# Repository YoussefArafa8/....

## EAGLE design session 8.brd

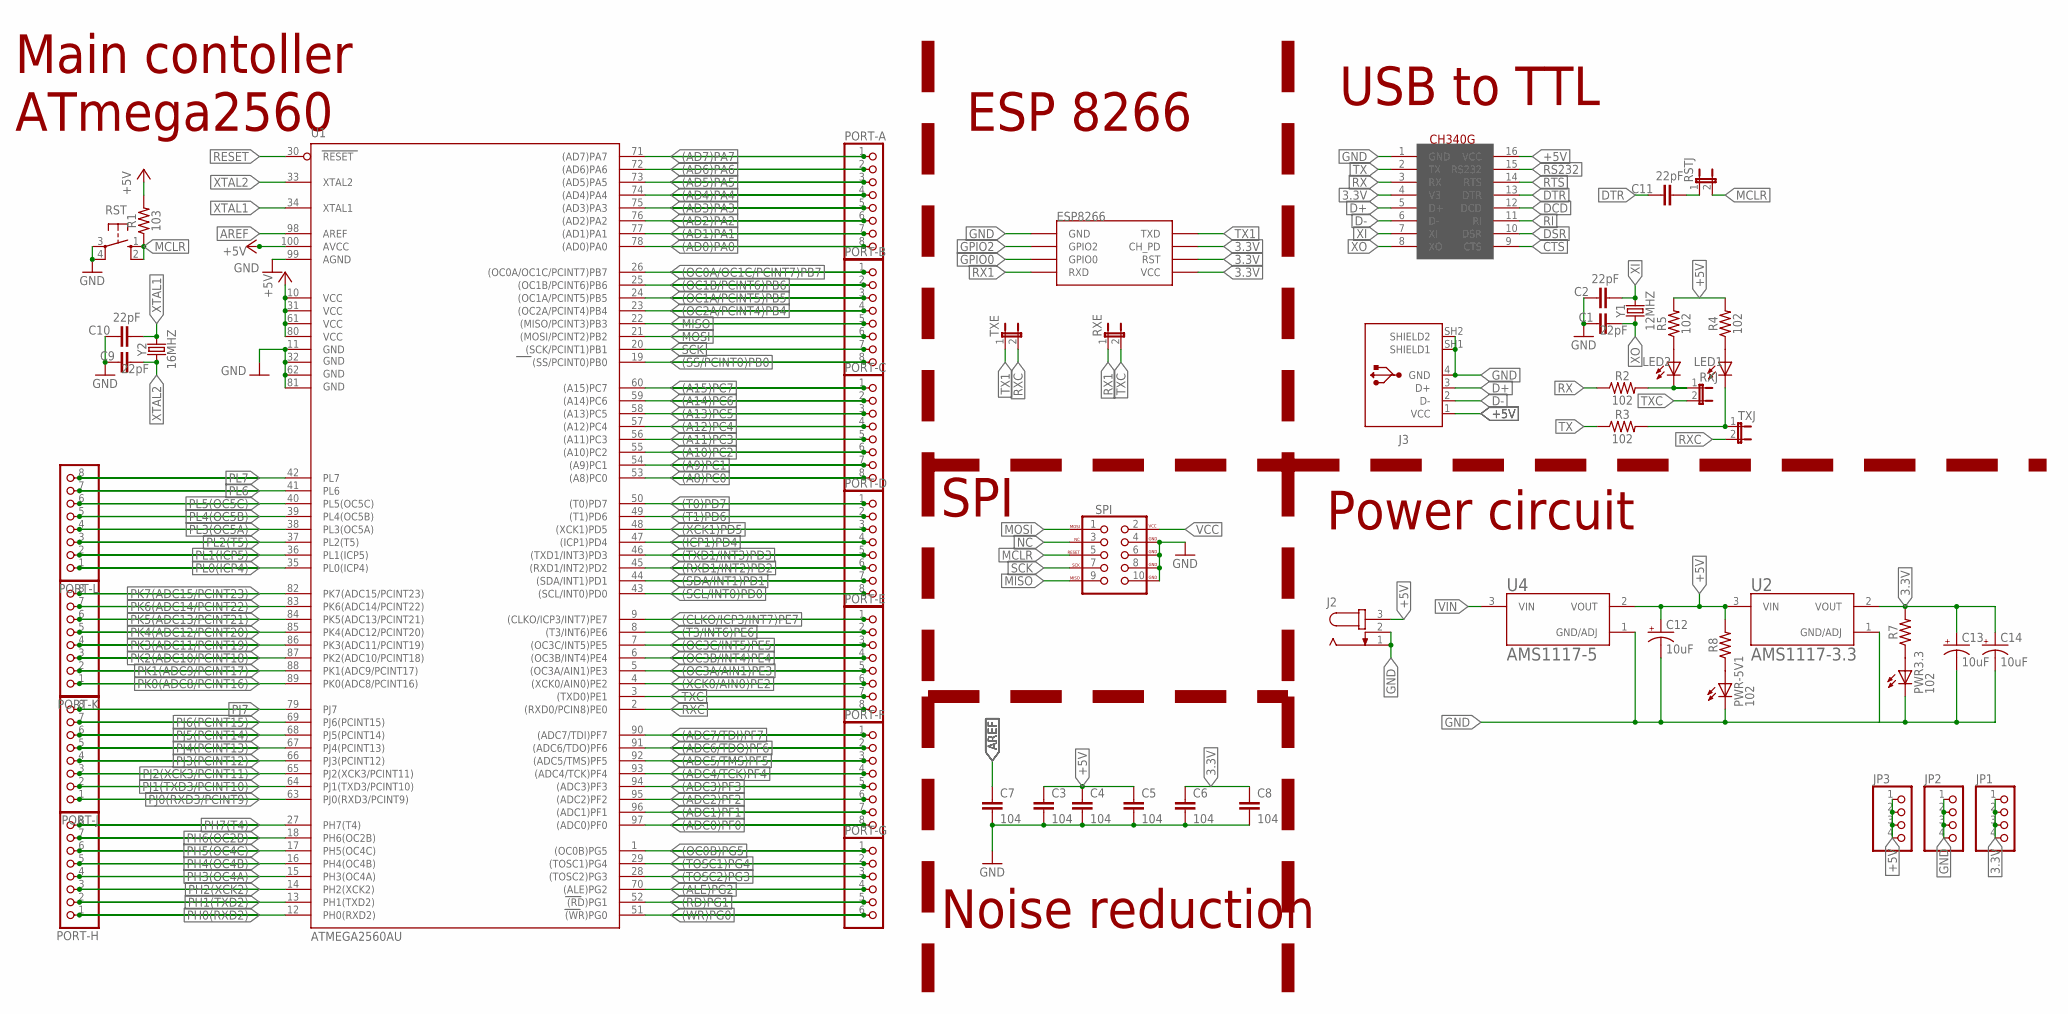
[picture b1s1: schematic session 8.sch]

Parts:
C1, C2, C9, C10, C11: 22pF; CAP-PTH-2.54
C3, C4, C5, C6, C7, C8: 104; CAP-PTH-SMALL-KIT
C12, C13, C14: 10uF; CPOL-RADIAL-2.5MM-5MM
ESP8266: ESP01
J2: JACK-PLUG1; SPC4078
J3: 61729-1011; 61729-1011BLF
JP1, JP2, JP3: PINHD-1X4; 1X04
LED1, LED2: LEDCHIP-LED0805; CHIP-LED0805
PORT-A: PINHD-1X8; 1X08
PORT-B: PINHD-1X8; 1X08
PORT-C: PINHD-1X8; 1X08
PORT-D: PINHD-1X8; 1X08
PORT-E: PINHD-1X8; 1X08
PORT-F: PINHD-1X8; 1X08
PORT-G: PINHD-1X6; 1X06
PORT-H: PINHD-1X8; 1X08
PORT-J: PINHD-1X8; 1X08
PORT-K: PINHD-1X8; 1X08
PORT-L: PINHD-1X8; 1X08
PWR3.3: 102; CHIP-LED0805
PWR-5V1: 102; CHIP-LED0805
R1: 103; 1206
R2, R3, R4, R5: 102; 1206
R7, R8: 1206
RST: 10-XX; B3F-10XX
RSTJ: JP1E; JP1
RXE: JP1E; JP1
RXJ: JP1E; JP1
SPI: AVR_SPI_PROG_5X2LOCK; 2X5-SHROUDED_LOCK
TXE: JP1E; JP1
TXJ: JP1E; JP1
U1: ATMEGA2560AU; TQFP100
U2: AMS1117-3.3; SOT229P700X180-4N
U4: AMS1117-5; SOT229P700X180-4N
U$2: CH340G; SOIC16
Y1: 12MHZ; HC49U
Y2: 16MHZ; HC49U

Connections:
3.3V: C6.1, C8.1, C13.1 (+), C14.1 (+), ESP8266.CH_PD, ESP8266.RST, ESP8266.VCC, JP1.1, JP1.2, JP1.3, JP1.4, R7.2, U2.2 (VOUT), U$2.4 (V3)
(A8)PC0: PORT-C.8, U1.53 ((A8)PC0)
(A9)PC1: PORT-C.7, U1.54 ((A9)PC1)
(A10)PC2: PORT-C.6, U1.55 ((A10)PC2)
(A11)PC3: PORT-C.5, U1.56 ((A11)PC3)
(A12)PC4: PORT-C.4, U1.57 ((A12)PC4)
(A13)PC5: PORT-C.3, U1.58 ((A13)PC5)
(A14)PC6: PORT-C.2, U1.59 ((A14)PC6)
(A15)PC7: PORT-C.1, U1.60 ((A15)PC7)
(AD0)PA0: PORT-A.8, U1.78 ((AD0)PA0)
(AD1)PA1: PORT-A.7, U1.77 ((AD1)PA1)
(AD2)PA2: PORT-A.6, U1.76 ((AD2)PA2)
(AD3)PA3: PORT-A.5, U1.75 ((AD3)PA3)
(AD4)PA4: PORT-A.4, U1.74 ((AD4)PA4)
(AD5)PA5: PORT-A.3, U1.73 ((AD5)PA5)
(AD6)PA6: PORT-A.2, U1.72 ((AD6)PA6)
(AD7)PA7: PORT-A.1, U1.71 ((AD7)PA7)
(ADC0)PF0: PORT-F.8, U1.97 ((ADC0)PF0)
(ADC1)PF1: PORT-F.7, U1.96 ((ADC1)PF1)
(ADC2)PF2: PORT-F.6, U1.95 ((ADC2)PF2)
(ADC3)PF3: PORT-F.5, U1.94 ((ADC3)PF3)
(ADC4/TCK)PF4: PORT-F.4, U1.93 ((ADC4/TCK)PF4)
(ADC5/TMS)PF5: PORT-F.3, U1.92 ((ADC5/TMS)PF5)
(ADC6/TDO)PF6: PORT-F.2, U1.91 ((ADC6/TDO)PF6)
(ADC7/TDI)PF7: PORT-F.1, U1.90 ((ADC7/TDI)PF7)
(ALE)PG2: PORT-G.4, U1.70 ((ALE)PG2)
(CLKO/ICP3/INT7)PE7: PORT-E.1, U1.9 ((CLKO/ICP3/INT7)PE7)
(ICP1)PD4: PORT-D.4, U1.47 ((ICP1)PD4)
(OC0A/OC1C/PCINT7)PB7: PORT-B.1, U1.26 ((OC0A/OC1C/PCINT7)PB7)
(OC0B)PG5: PORT-G.1, U1.1 ((OC0B)PG5)
(OC1A/PCINT5)PB5: PORT-B.3, U1.24 ((OC1A/PCINT5)PB5)
(OC1B/PCINT6)PB6: PORT-B.2, U1.25 ((OC1B/PCINT6)PB6)
(OC2A/PCINT4)PB4: PORT-B.4, U1.23 ((OC2A/PCINT4)PB4)
(OC3A/AIN1)PE3: PORT-E.5, U1.5 ((OC3A/AIN1)PE3)
(OC3B/INT4)PE4: PORT-E.4, U1.6 ((OC3B/INT4)PE4)
(OC3C/INT5)PE5: PORT-E.3, U1.7 ((OC3C/INT5)PE5)
(RD)PG1: PORT-G.5, U1.52 ((RD)PG1)
(RXD1/INT2)PD2: PORT-D.6, U1.45 ((RXD1/INT2)PD2)
(SCL/INT0)PD0: PORT-D.8, U1.43 ((SCL/INT0)PD0)
(SDA/INT1)PD1: PORT-D.7, U1.44 ((SDA/INT1)PD1)
(SS/PCINT0)PB0: PORT-B.8, U1.19 ((SS/PCINT0)PB0)
(T0)PD7: PORT-D.1, U1.50 ((T0)PD7)
(T1)PD6: PORT-D.2, U1.49 ((T1)PD6)
(T3/INT6)PE6: PORT-E.2, U1.8 ((T3/INT6)PE6)
(TOSC1)PG4: PORT-G.2, U1.29 ((TOSC1)PG4)
(TOSC2)PG3: PORT-G.3, U1.28 ((TOSC2)PG3)
(TXD1/INT3)PD3: PORT-D.5, U1.46 ((TXD1/INT3)PD3)
(WR)PG0: PORT-G.6, U1.51 ((WR)PG0)
(XCK0/AIN0)PE2: PORT-E.6, U1.4 ((XCK0/AIN0)PE2)
(XCK1)PD5: PORT-D.3, U1.48 ((XCK1)PD5)
+5V: C3.1, C4.1, C5.1, C12.1 (+), J2.3, J3.1 (VCC), JP3.1, JP3.2, JP3.3, JP3.4, R1.2, R4.2, R5.2, R8.2, U1.10 (VCC), U1.31 (VCC1), U1.61 (VCC2), U1.80 (VCC3), U1.100 (AVCC), U2.3 (VIN), U4.2 (VOUT), U$2.16 (VCC)
AREF: C7.1, U1.98 (AREF)
CTS: U$2.9 (CTS)
D+: J3.3 (D+), U$2.5 (D+)
D-: J3.2 (D-), U$2.6 (D-)
DCD: U$2.12 (DCD)
DSR: U$2.10 (DSR)
DTR: C11.1, U$2.13 (DTR)
GND: C1.1, C2.1, C3.2, C4.2, C5.2, C6.2, C7.2, C8.2, C9.1, C10.1, C12.2 (-), C13.2 (-), C14.2 (-), ESP8266.GND, J2.1, J2.2, J3.4 (GND), J3.SH1 (SHIELD1), J3.SH2 (SHIELD2), JP2.1, JP2.2, JP2.3, JP2.4, PWR3.3.C, PWR-5V1.C, RST.3, RST.4 (P1), SPI.4 (GND), SPI.6 (GND), SPI.8 (GND), SPI.10 (GND), U1.11 (GND), U1.32 (GND1), U1.62 (GND2), U1.81 (GND3), U1.99 (AGND), U2.1 (GND/ADJ), U4.1 (GND/ADJ), U$2.1 (GND)
GPIO0: ESP8266.GPIO0
GPIO2: ESP8266.GPIO2
MCLR: R1.1, RST.1 (S), RST.2 (S1), RSTJ.2, SPI.5 (RESET)
MISO: PORT-B.5, SPI.9 (MISO), U1.22 ((MISO/PCINT3)PB3)
MOSI: PORT-B.6, SPI.1 (MOSI), U1.21 ((MOSI/PCINT2)PB2)
unnamed: LED1.A, R4.1
unnamed: C11.2, RSTJ.1
unnamed: LED2.A, R5.1
unnamed: PWR3.3.A, R7.1
unnamed: PWR-5V1.A, R8.1
NC: SPI.3 (NC)
PH0(RXD2): PORT-H.1, U1.12 (PH0(RXD2))
PH1(TXD2): PORT-H.2, U1.13 (PH1(TXD2))
PH2(XCK2): PORT-H.3, U1.14 (PH2(XCK2))
PH3(OC4A): PORT-H.4, U1.15 (PH3(OC4A))
PH4(OC4B): PORT-H.5, U1.16 (PH4(OC4B))
PH5(OC4C): PORT-H.6, U1.17 (PH5(OC4C))
PH6(OC2B): PORT-H.7, U1.18 (PH6(OC2B))
PH7(T4): PORT-H.8, U1.27 (PH7(T4))
PJ0(RXD3/PCINT9): PORT-J.1, U1.63 (PJ0(RXD3/PCINT9))
PJ1(TXD3/PCINT10): PORT-J.2, U1.64 (PJ1(TXD3/PCINT10))
PJ2(XCK3/PCINT11): PORT-J.3, U1.65 (PJ2(XCK3/PCINT11))
PJ3(PCINT12): PORT-J.4, U1.66 (PJ3(PCINT12))
PJ4(PCINT13): PORT-J.5, U1.67 (PJ4(PCINT13))
PJ5(PCINT14): PORT-J.6, U1.68 (PJ5(PCINT14))
PJ6(PCINT15): PORT-J.7, U1.69 (PJ6(PCINT15))
PJ7: PORT-J.8, U1.79 (PJ7)
PK0(ADC8/PCINT16): PORT-K.1, U1.89 (PK0(ADC8/PCINT16))
PK1(ADC9/PCINT17): PORT-K.2, U1.88 (PK1(ADC9/PCINT17))
PK2(ADC10/PCINT18): PORT-K.3, U1.87 (PK2(ADC10/PCINT18))
PK3(ADC11/PCINT19): PORT-K.4, U1.86 (PK3(ADC11/PCINT19))
PK4(ADC12/PCINT20): PORT-K.5, U1.85 (PK4(ADC12/PCINT20))
PK5(ADC13/PCINT21): PORT-K.6, U1.84 (PK5(ADC13/PCINT21))
PK6(ADC14/PCINT22): PORT-K.7, U1.83 (PK6(ADC14/PCINT22))
PK7(ADC15/PCINT23): PORT-K.8, U1.82 (PK7(ADC15/PCINT23))
PL0(ICP4): PORT-L.1, U1.35 (PL0(ICP4))
PL1(ICP5): PORT-L.2, U1.36 (PL1(ICP5))
PL2(T5): PORT-L.3, U1.37 (PL2(T5))
PL3(OC5A): PORT-L.4, U1.38 (PL3(OC5A))
PL4(OC5B): PORT-L.5, U1.39 (PL4(OC5B))
PL5(OC5C): PORT-L.6, U1.40 (PL5(OC5C))
PL6: PORT-L.7, U1.41 (PL6)
PL7: PORT-L.8, U1.42 (PL7)
RESET: U1.30 (RESET)
RI: U$2.11 (RI)
RS232: U$2.15 (RS232)
RTS: U$2.14 (RTS)
RX: R2.1, U$2.3 (RX)
RX0: LED1.C, R3.2, TXJ.1
RX1: ESP8266.RX (RXD), RXE.1
RXC: PORT-E.8, TXE.2, TXJ.2, U1.2 ((RXD0/PCIN8)PE0)
SCK: PORT-B.7, SPI.7 (SCK), U1.20 ((SCK/PCINT1)PB1)
TX: R3.1, U$2.2 (TX)
TX0: LED2.C, R2.2, RXJ.1
TX1: ESP8266.TX (TXD), TXE.1
TXC: PORT-E.7, RXE.2, RXJ.2, U1.3 ((TXD0)PE1)
VCC: SPI.2 (VCC)
VIN: U4.3 (VIN)
XI: C2.2, U$2.7 (XI), Y1.2
XO: C1.2, U$2.8 (XO), Y1.1
XTAL1: C10.2, U1.34 (XTAL1), Y2.2
XTAL2: C9.2, U1.33 (XTAL2), Y2.1

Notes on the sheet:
Main contoller ATmega2560
ESP 8266
SPI
Noise reduction
USB to TTL
Power circuit

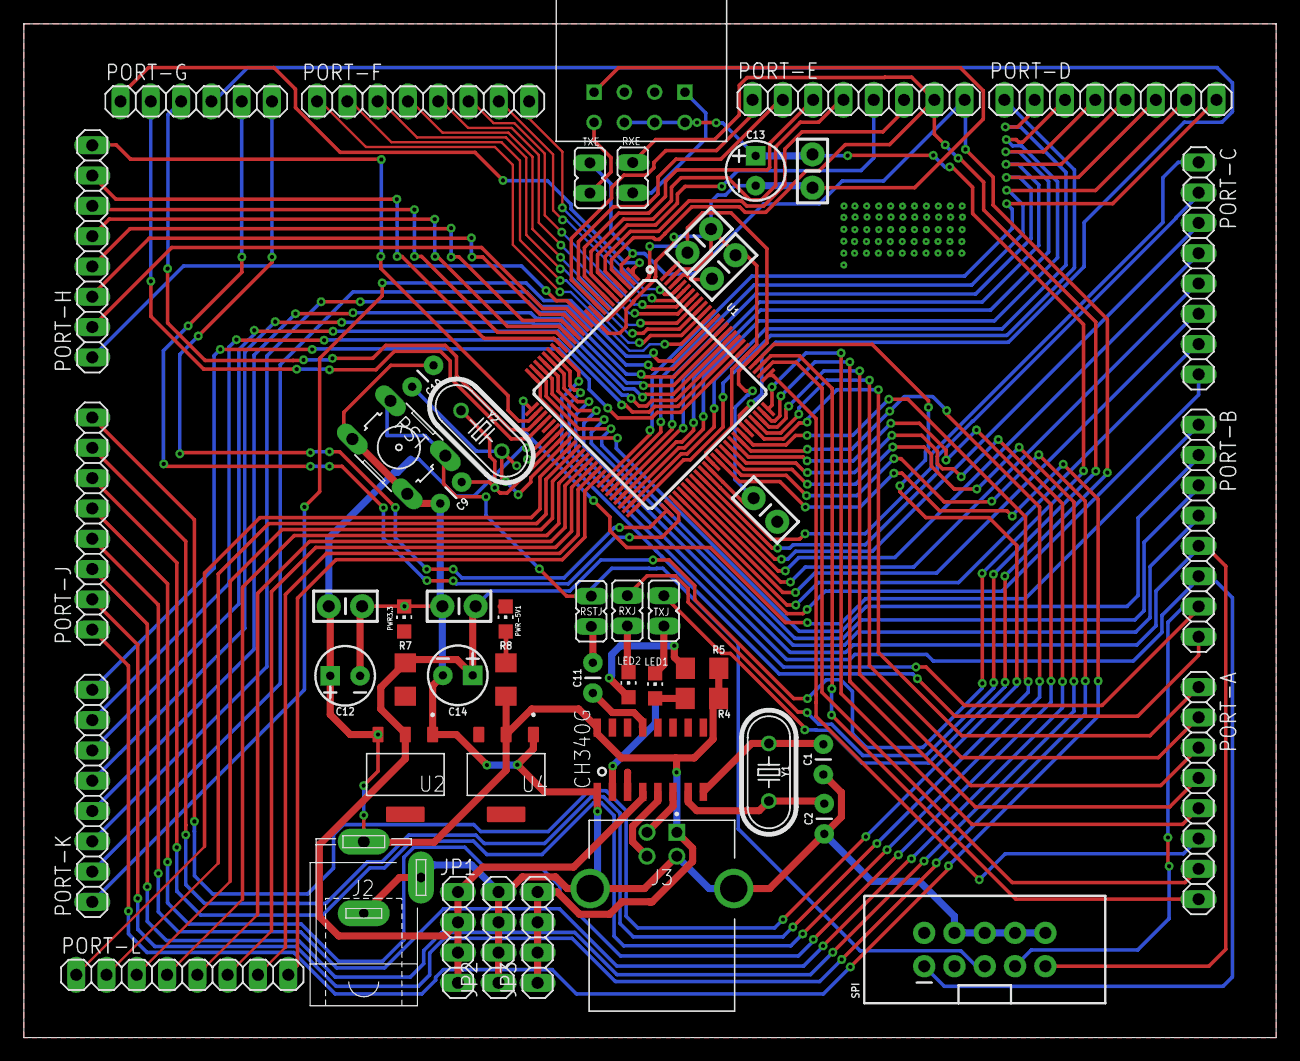
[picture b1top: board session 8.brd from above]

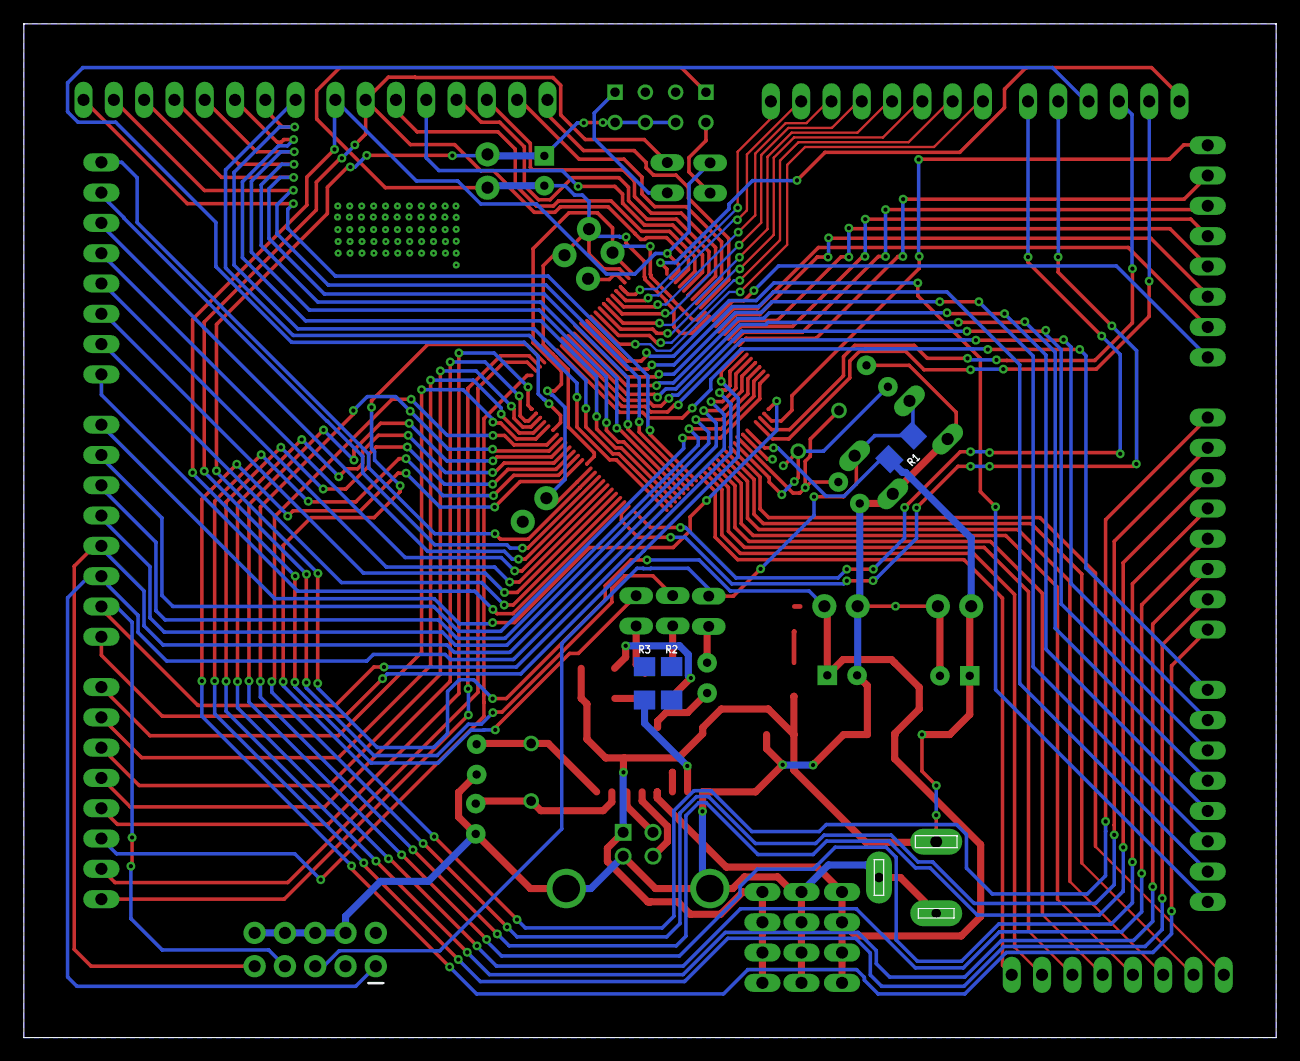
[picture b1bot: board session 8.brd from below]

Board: 2 copper layers, 105.0 x 85.0 mm, 55 parts (3 on the bottom side), 109 nets.

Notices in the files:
parts and their libraries:
SparkFun-Capacitors: Licensing: Creative Commons ShareAlike 4.0 International - https://creativecommons.org/licenses/by-sa/4.0
